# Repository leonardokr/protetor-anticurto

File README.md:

asasa
# Protetor anti-curto com relé
Protetor com desarme por relé para proteção de circuitos eletrônicos.

Características:
- O relé e resistores podem ser dimensionados para outras tensões
- Ao manter o curto o circuito não rearma
- Conectores para LEDs e botão externos (para montagem em cases)
- Tecnologia PTH e placa de uma face para ser possível montar com ferramentas básicas

Projetos esquemáticos e de layout de placas desenvolvidos em Eagle 9.2.0 e Fusion 360.
Bibliotecas personalizadas de produtos genéricos/equivalentes fornecidas no repositório.

###### Bibliotecas personalizadas
* [Conectores KRE](https://github.com/leonardokr/eagle-conectores-kre) - Conectores utilizados na placa para facilitar montagem e manutenção

## Resumo
<p>
Esquema do circuito e da placa feitos no Eagle, é em placa simples e componentes PTH. As dimensões são pequenas e os conectores de entrada e saída são para fácil conexão e troca, mas podem ser soldados fios diretamente na furação.
</p>

<br/>
<p>
Imagem da placa gerada, assim como o esquema de furação (os arquivos PDF com tamanho real estão no projeto):
</p>

<hr/>
<p>
  Download dos arquivos, sendo: Cima; Cima (espelhado); Fundo; Fundo (espelhado); Furação; Furação (espelhado).
</p>
<p align="center">

</p>
<br/>

###### Imagens 3D do projeto da placa:
<p align="center">

</p>

###### Arquivos 3D
<br>
<p>
  Download dos arquivos, sendo: F3D; SKP; OBJ; DWG.
</p>
<p align="center">

</p>
<hr>

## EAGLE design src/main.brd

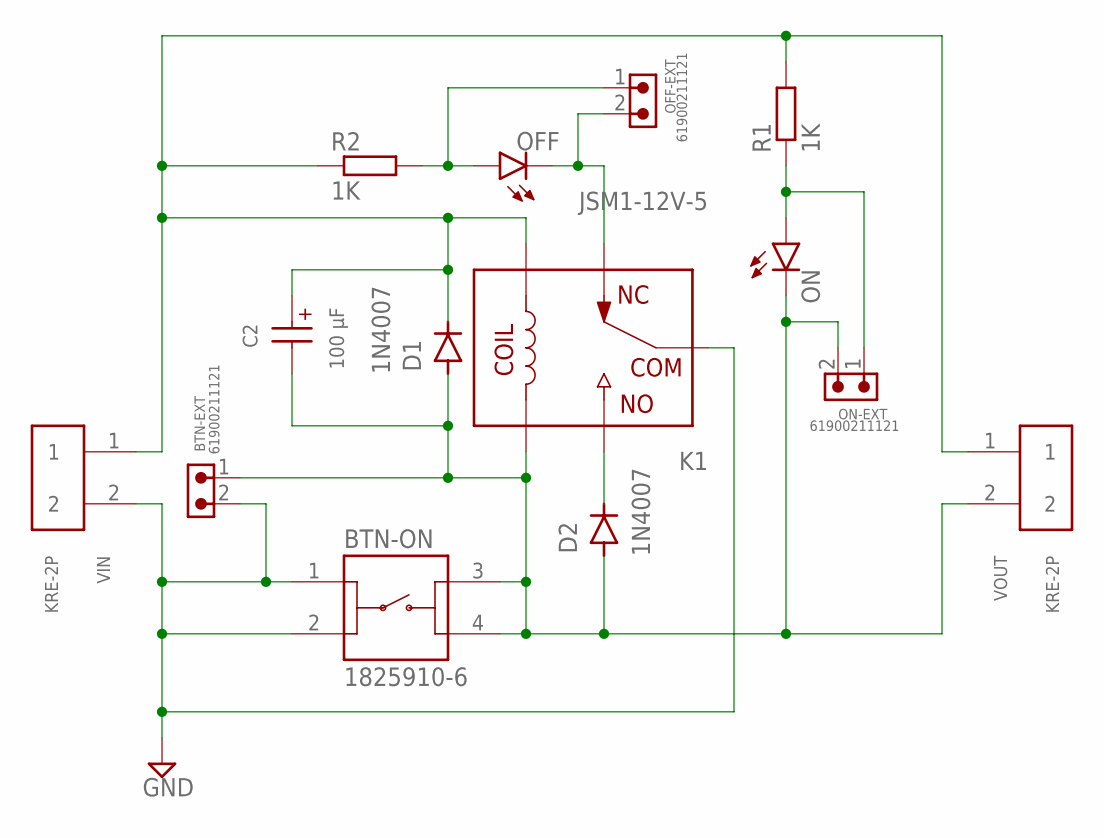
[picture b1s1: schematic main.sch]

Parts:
BTN-EXT: 61900211121
BTN-ON: 1825910-6
C2: 100 µF; WCAP-ATLL_5X11(DXL)
D1, D2: 1N4007; DO-41
K1: JSM1-12V-5
OFF: LED-CIRCULAR-3MM-VERMELHO; LED-CIR-3MM-VERMELHO
OFF-EXT: 61900211121
ON: LED-CIRCULAR-3MM-VERDE; LED-CIR-3MM-VERDE
ON-EXT: 61900211121
R1, R2: 1K; 0207/7
VIN: KRE-2P
VOUT: KRE-2P

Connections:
GND: BTN-EXT.2, BTN-ON.1, BTN-ON.2, K1.1, VIN.2
unnamed: BTN-EXT.1, BTN-ON.3, BTN-ON.4, C2.2 (-), D1.A, D2.A, K1.2, ON.K (CATHODE), ON-EXT.2, VOUT.2
unnamed: OFF.A (ANODE), OFF-EXT.1, R2.2
unnamed: C2.1 (+), D1.C, K1.5, R1.2, R2.1, VIN.1, VOUT.1
unnamed: K1.4, OFF.K (CATHODE), OFF-EXT.2
unnamed: ON.A (ANODE), ON-EXT.1, R1.1
unnamed: D2.C, K1.3

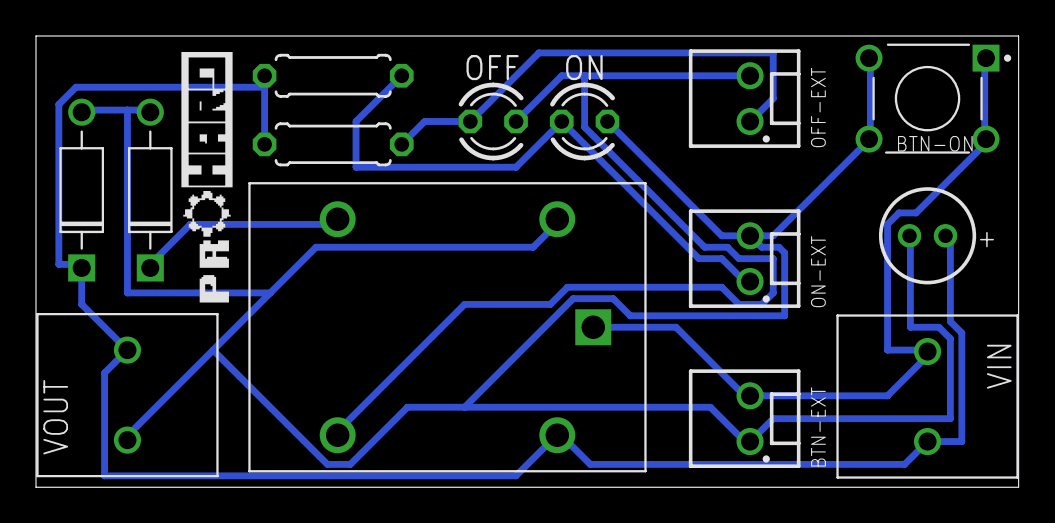
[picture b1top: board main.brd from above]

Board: 2 copper layers, 54.6 x 25.1 mm, 14 parts (0 on the bottom side), 7 nets.

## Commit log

2020-11-21 Criação do README
2020-11-21 On branch main
2020-11-21 On branch v0.1pre
2021-08-24 Alteração de teste em nova branch
    Adicionado texto temporário no topo da página

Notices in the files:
parts and their libraries:
Wurth_Connectors_WR-WTB: Copyright: Würth Elektronik
